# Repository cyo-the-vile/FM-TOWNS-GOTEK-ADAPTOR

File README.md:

# FM-TOWNS-GOTEK-ADAPTOR
An FM Towns floppy emulator adaptor board

I purchased my first FM TOWNS computer to restore and after restoring it I found out both my floppy drives didn't work! No matter what I did to try to bring them back to life! So I sought to make a solution so I can replace the floppy drive with something modern.

The intent with this adaptor board is to use it to replace the floppy drive of an FM Towns computer very specifically Tower models for a floppy emulator like a GOTEK or HXC.  Im personally using goteks with flashfloppy firmware and they work extremely well with my CX20 and 20F.  This adaptor should work for any Towns PC with the TEAC drives. The UX20 I own is compatible as well. Some people report MX and MA models work but I don't own these to confirm.

To summarize: It is confirmed for the tower models and U* models as they used the same base family of parts.  A Fresh model doesn't need this adaptor board.  If you are unsure take the floppy drive out of your computer. If it is the floppy drive below, you will need this adaptor board if you want to use a floppy drive emulator.

Pins 7, 9 and 11 coming OUT of the computer backplane card are confirmed to be 5 volts.  They're embedded between the ground pins and I fried two GOTEKs figuring this out. That is why you need this board.

When installing this PCB on the back of your gotek it has a very tight fit in the computer and I would strongly advise not screwing the GOTEK into the floppy cradle.

https://fb.watch/2Kf5oHgrxs/

This is a video showing the installation of this board with a Gotek with flashfloppy firmware in a CX20.  At a later time I will have a japanese language installation guide or video.

There will be 3 conditions when you finally fit this inside the computer:

-The computer will not start.  However once you take the gotek out the computer will turn on.  This is a grounding issue.  Simply turn it off and try fitting it inside again

-The gotek will turn on showing the firmware but not loading or showing any floppy disc images.  Bad fit and turn the PC off and try again

-The gotek will turn on showing a disc image on the USB stick.  When you start seeing it load tracks then you have successfully fit this into the computer!

It is impossible to brick the gotek with this board.

PAY ATTENTION TO THE PHOTOS YOU SEE TO INSTALL THIS PROPERLY. IT IS EASY TO MAKE A MISTAKE AND SOLDER THE CONNECTORS IMPROPERLY

Bill of material:

HWS5348  	2x17 pin Snap Header .1"sp R/A	

HWS15789	2x17 pin Female Header .1"sp R/A

Female arduino pin header 2.54mm size 

In this photo the orange female jumper is 5V and the yellow wire is GND. Plug them into the appropriate spot on the floppy emulator to power it properly.  If you mix them up you will brick your floppy emulator.

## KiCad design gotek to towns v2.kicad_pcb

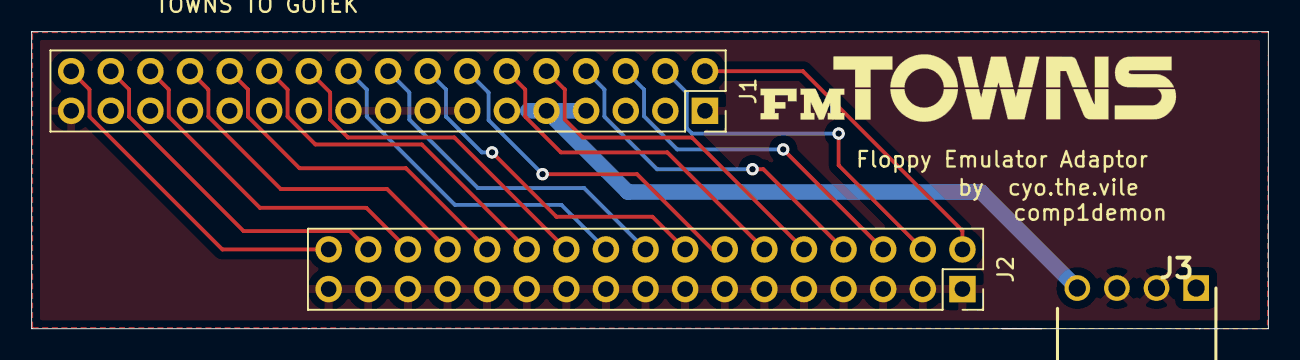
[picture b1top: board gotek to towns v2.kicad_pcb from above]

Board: 2 copper layers, 79.3 x 19.0 mm, 3 parts (0 on the bottom side), 19 nets.

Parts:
J1: Towns; PinSocket_2x17_P2.54mm_Vertical
J2: GOTEK; PinSocket_2x17_P2.54mm_Vertical
J3: 801-87-004-20-001101; SHDRRA4W62P0X254_1X4_1016X700X254P

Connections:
/5V: J1.7, J1.9, J1.11, J3.4
/DC: J1.2, J2.2
/DIR: J1.18, J2.18
/DS0: J1.10, J2.10
/DS1: J1.12, J2.12
/DS2: J1.14, J2.14
/DS3: J1.6, J2.6
/GND: J1.1, J1.5, J1.13, J1.15, J1.17, J1.19, J1.21, J1.23, J1.25, J1.27, J1.29, J1.31, J1.33, J2.1, J2.3, J2.5, J2.7, J2.9, J2.11, J2.13, J2.15, J2.17, J2.19, J2.21, J2.23, J2.25, J2.27, J2.29, J2.31, J2.33, J3.2, J3.3
/IDX: J1.8, J2.8
/IV: J1.4, J2.4
/MON: J1.16, J2.16
/RD: J1.30, J2.30
/RDY: J1.34, J2.34
/SIS: J1.32, J2.32
/STP: J1.20, J2.20
/TOO: J1.26, J2.26
/WC: J1.24, J2.24
/WO: J1.22, J2.22
/WP: J1.28, J2.28

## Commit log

2021-01-01 Add files via upload
    -Added zipped GERBER files for fabrication
    -Added KiCAD source documents
